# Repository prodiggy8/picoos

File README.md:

##### PicoOS

A bare-metal, very simple operating system for the RP2040/RPI Pico-W written in Rust. Built on [Embassy](https://embassy.dev/).

**Features**

- shell with Unix-like commands
- SD card support with a FAT32-like file system
- text display via DVI, based on [DusterTheFirst's implementation](https://github.com/DusterTheFirst/pico-dvi-rs) 
- PS2 keyboard input via PIO
- run programs with syscalls (print, read)
- load and execute ELF binaries
- CYW43 wireless support
- TCP/IP stack via embassy-net
- debug with websockets

##### Prerequisites

- [Rust](https://rustup.rs/) with `thumbv6m-none-eabi` target
- [probe-rs](https://probe.rs/) for flashing (or [elf2uf2-rs](https://crates.io/crates/elf2uf2-rs) for USB boot mode)
- See PCB above for details on peripherals

##### Build & Run

```bash
cargo run
```

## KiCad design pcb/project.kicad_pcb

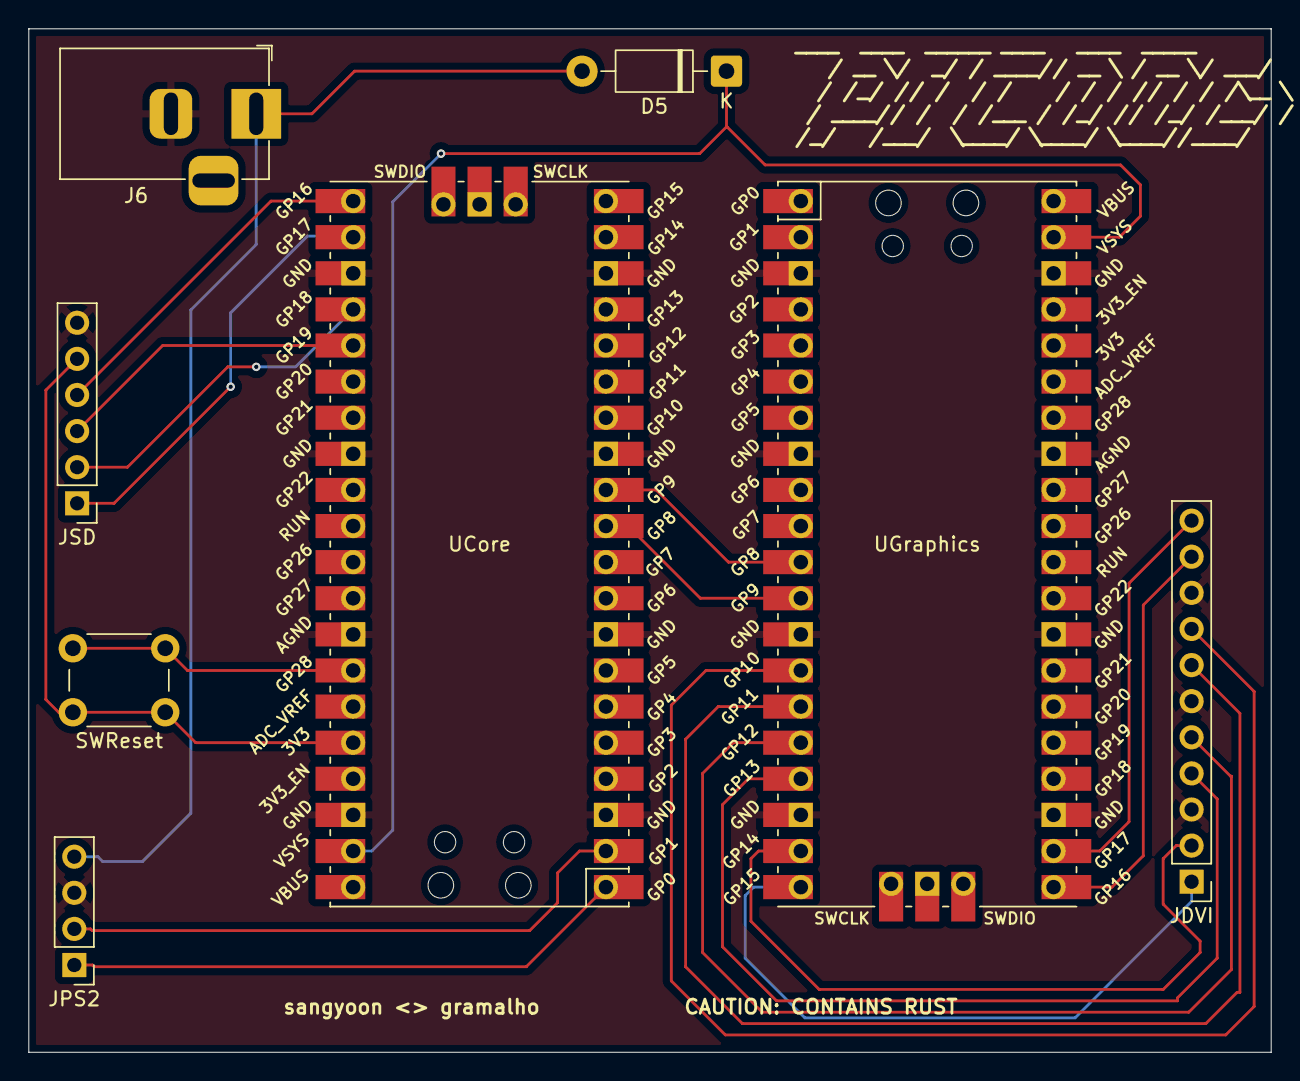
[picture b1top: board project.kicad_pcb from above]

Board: 2 copper layers, 87.4 x 72.0 mm, 8 parts (0 on the bottom side), 21 nets.

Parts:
D5: 1N4001; D_DO-41_SOD81_P10.16mm_Horizontal
J6: Barrel_Jack; BarrelJack_Horizontal
JDVI: Conn_01x11_Pin; PinHeader_1x11_P2.54mm_Vertical
JPS2: Conn_01x04_Pin; PinHeader_1x04_P2.54mm_Vertical
JSD: Conn_01x06_Pin; PinHeader_1x06_P2.54mm_Vertical
SWReset: SW_Push; SW_PUSH_6mm
UCore: Pico W - Core; RPi_Pico_SMD_TH
UGraphics: Pico DVI; RPi_Pico_SMD_TH

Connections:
+3.3V: JSD.5, SWReset.1, UCore.36 (3V3)
+5V: D5.2 (A), J6.1, JPS2.4
CS: JSD.1, UCore.22 (GPIO17)
GND: J6.2, JDVI.3, JDVI.6, JDVI.9, JPS2.3, JSD.6, UCore.3 (GND), UCore.8 (GND), UCore.13 (GND), UCore.18 (GND), UCore.23 (GND), UCore.28 (GND), UCore.33 (AGND), UCore.38 (GND), UGraphics.3 (GND), UGraphics.8 (GND), UGraphics.13 (GND), UGraphics.18 (GND), UGraphics.23 (GND), UGraphics.28 (GND), UGraphics.33 (AGND), UGraphics.38 (GND)
KEY_CLK: JPS2.2, UCore.2 (GPIO1)
KEY_DATA: JPS2.1, UCore.1 (GPIO0)
MISO: JSD.4, UCore.21 (GPIO16)
MOSI: JSD.3, UCore.25 (GPIO19)
POWER: D5.1 (K), UCore.39 (VSYS), UGraphics.39 (VSYS)
RXDVI: UCore.11 (GPIO8), UGraphics.12 (GPIO9)
S0: SWReset.2, UCore.34 (GPIO28_ADC2)
SCK: JSD.2, UCore.24 (GPIO18)
T0+: JDVI.5, UGraphics.16 (GPIO12)
T0-: JDVI.4, UGraphics.17 (GPIO13)
T1+: JDVI.8, UGraphics.14 (GPIO10)
T1-: JDVI.7, UGraphics.15 (GPIO11)
T2+: JDVI.11, UGraphics.22 (GPIO17)
T2-: JDVI.10, UGraphics.21 (GPIO16)
TC+: JDVI.2, UGraphics.19 (GPIO14)
TC-: JDVI.1, UGraphics.20 (GPIO15)
TXDVI: UCore.12 (GPIO9), UGraphics.11 (GPIO8)

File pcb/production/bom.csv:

Designator,Footprint,Quantity,Value,LCSC Part #
D5,D_DO-41_SOD81_P10.16mm_Horizontal,1,1N4001,
J6,BarrelJack_Horizontal,1,Barrel_Jack,
JDVI,PinHeader_1x11_P2.54mm_Vertical,1,Conn_01x11_Pin,
JPS2,PinHeader_1x04_P2.54mm_Vertical,1,Conn_01x04_Pin,
JSD,PinHeader_1x06_P2.54mm_Vertical,1,Conn_01x06_Pin,
SWRESET,SW_PUSH_6mm,1,SW_Push,
UCORE,RPi_Pico_SMD_TH,1,Pico W - Core,
UGRAPHICS,RPi_Pico_SMD_TH,1,Pico DVI,

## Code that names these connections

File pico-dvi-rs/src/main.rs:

#![no_std]
#![no_main]

extern crate alloc;

use core::{arch::global_asm, cell::UnsafeCell, mem::MaybeUninit};

use defmt_rtt as _;
use panic_probe as _; // TODO: remove if you need 5kb of space, since panicking + formatting machinery is huge

use cortex_m::peripheral::NVIC;
use defmt::info;
use dvi::dma::DmaChannelList;
use embedded_alloc::Heap;
use rp_pico::{
    hal::{
        clocks::Clock,
        dma::{Channel, DMAExt, CH0, CH1, CH2, CH3, CH4, CH5},
        gpio::PinState,
        multicore::{Multicore, Stack},
        pwm,
        sio::{Sio, SioFifo},
        watchdog::Watchdog,
        uart::{DataBits, StopBits, UartConfig, UartPeripheral},
    },
    pac::{self, interrupt},
    Pins,
};
use fugit::RateExtU32;

use pac::Interrupt;

use crate::{
    clock::init_clocks,
    dvi::{
        core1_main,
        dma::DmaChannels,
        serializer::{DviClockPins, DviDataPins, DviSerializer},
        timing::VGA_TIMING,
        DviInst,
    },
    render::{init_4bpp_palette, init_display_swapcell, render_line, GLOBAL_PALETTE},
};

mod clock;
mod demo;
mod dvi;
mod link;
mod render;
mod scanlist;

#[global_allocator]
static HEAP: Heap = Heap::empty();

global_asm! {
    include_str!("pre_init.asm"),
    options(raw)
}

struct DviChannels;
impl DmaChannelList for DviChannels {
    type Ch0 = Channel<CH0>;
    type Ch1 = Channel<CH1>;
    type Ch2 = Channel<CH2>;
    type Ch3 = Channel<CH3>;
    type Ch4 = Channel<CH4>;
    type Ch5 = Channel<CH5>;
}

struct DviInstWrapper(UnsafeCell<MaybeUninit<DviInst<DviChannels>>>);

// Safety: access to the instance is indeed shared across threads,
// as it is initialized in the main thread and the interrupt should
// be modeled as another thread (and may be on a different core),
// but only one has access at a time.
//
// Note: this is annoying, `static mut` is more ergonomic (but less
// precise). When `SyncUnsafeCell` is stabilized, use that instead.
unsafe impl Sync for DviInstWrapper {}

static DVI_INST: DviInstWrapper = DviInstWrapper(UnsafeCell::new(MaybeUninit::uninit()));

static mut CORE1_STACK: Stack<256> = Stack::new();

static mut FIFO: MaybeUninit<SioFifo> = MaybeUninit::uninit();

// Separate macro annotated function to make rust-analyzer fixes apply better
#[rp_pico::entry]
fn macro_entry() -> ! {
    entry();
}

const PALETTE: &[u32; 16] = &[
    0x000000, 0xffffff, 0x9d9d9d, 0xe06f8b, 0xbe2633, 0x493c2b, 0xa46422, 0xeb8931, 0xf7e26b,
    0xa3ce27, 0x44891a, 0x2f484e, 0x1b2632, 0x5784, 0x31a2f2, 0xb2dcef,
];

fn entry() -> ! {
    info!("Program start");

    // Test allocations in different memory regions
    rom();
    ram();
    ram_x();
    ram_y();
    defmt::info!("If we have not panicked by now, memory regions probably work well");

    {
        const HEAP_SIZE: usize = 128 * 1024;
        static mut HEAP_MEM: [MaybeUninit<u8>; HEAP_SIZE] = [MaybeUninit::uninit(); HEAP_SIZE];
        unsafe { HEAP.init(HEAP_MEM.as_ptr() as usize, HEAP_SIZE) }
    }

    let mut peripherals = pac::Peripherals::take().unwrap();
    //let core_peripherals = pac::CorePeripherals::take().unwrap();

    sysinfo(&peripherals.SYSINFO);

    let mut watchdog = Watchdog::new(peripherals.WATCHDOG);
    let single_cycle_io = Sio::new(peripherals.SIO);

    let timing = VGA_TIMING;

    // External high-speed crystal on the pico board is 12Mhz
    let _clocks = init_clocks(
        peripherals.XOSC,
        peripherals.ROSC,
        peripherals.CLOCKS,
        peripherals.PLL_SYS,
        peripherals.PLL_USB,
        &mut peripherals.RESETS,
        &mut watchdog,
        timing.bit_clk,
    );

    let pins = Pins::new(
        peripherals.IO_BANK0,
        peripherals.PADS_BANK0,
        single_cycle_io.gpio_bank0,
        &mut peripherals.RESETS,
    );

    let led_pin = pins.led.into_push_pull_output_in_state(PinState::Low);

    let pwm_slices = pwm::Slices::new(peripherals.PWM, &mut peripherals.RESETS);
    let dma = peripherals.DMA.split(&mut peripherals.RESETS);

    let (data_pins, clock_pins) = {
        (
            DviDataPins {
                // 0
                blue_pos: pins.gpio12.into_function(),
                blue_neg: pins.gpio13.into_function(),
                // 1
                green_pos: pins.gpio10.into_function(),
                green_neg: pins.gpio11.into_function(),
                // 2
                red_pos: pins.gpio17.into_function(),
                red_neg: pins.gpio16.into_function(),
            },
            DviClockPins {
                clock_pos: pins.gpio14.into_function(),
                clock_neg: pins.gpio15.into_function(),
                pwm_slice: pwm_slices.pwm7,
            },
        )
    };

    let serializer = DviSerializer::new(
        peripherals.PIO0,
        &mut peripherals.RESETS,
        data_pins,
        clock_pins,
    );

    let dma_channels = DmaChannels::new(
        (dma.ch0, dma.ch1, dma.ch2, dma.ch3, dma.ch4, dma.ch5),
        serializer.tx(),
    );

    {
        // Safety: the DMA_IRQ_0 handler is not enabled yet. We have exclusive access to this static.
        let inst = unsafe { (*DVI_INST.0.get()).write(DviInst::new(timing, dma_channels)) };
        inst.setup_dma();
        inst.start();
    }
    let mut fifo = single_cycle_io.fifo;
    let mut mc = Multicore::new(&mut peripherals.PSM, &mut peripherals.PPB, &mut fifo);
    let cores = mc.cores();
    let core1 = &mut cores[1];
    core1
        .spawn(unsafe { &mut CORE1_STACK.mem }, move || {
            core1_main(serializer)
        })
        .unwrap();
    // Safety: enable interrupt for fifo to receive line render requests.
    // Transfer ownership of this end of the fifo to the interrupt handler.
    unsafe {
        FIFO = MaybeUninit::new(fifo);
        NVIC::unmask(Interrupt::SIO_IRQ_PROC0);
    }
    init_display_swapcell(640);

    unsafe {
        init_4bpp_palette(&mut GLOBAL_PALETTE, PALETTE);
    }

    let uart_pins = (
        pins.gpio8.into_function::<rp_pico::hal::gpio::FunctionUart>(),
        pins.gpio9.into_function::<rp_pico::hal::gpio::FunctionUart>(),
    );

    let mut uart = UartPeripheral::new(peripherals.UART1, uart_pins, &mut peripherals.RESETS)
        .enable(
            UartConfig::new(9600.Hz(), DataBits::Eight, None, StopBits::One),
            _clocks.peripheral_clock.freq(),
        )
        .unwrap();

    demo::demo(led_pin, &mut uart);
}

fn sysinfo(sysinfo: &pac::SYSINFO) {
    let is_fpga = sysinfo.platform.read().fpga().bit();
    let is_asic = sysinfo.platform.read().asic().bit();
    let git_hash = sysinfo.gitref_rp2040.read().bits();
    let manufacturer = sysinfo.chip_id.read().manufacturer().bits();
    let part = sysinfo.chip_id.read().part().bits();
    let revision = sysinfo.chip_id.read().revision().bits();

    info!(
        "SYSINFO
platform:
    FPGA: {=bool}
    ASIC: {=bool}
gitref_rp2040: {=u32:x}
chip_id:
    manufacturer: {=u16:X}
    part:         {=u16}
    revision:     {=u8}",
        is_fpga, is_asic, git_hash, manufacturer, part, revision
    );
}

// Functions and statics are placed in rom by default
fn rom() {
    let ptr = rom as fn() as *const ();
    defmt::assert!(
        (0x10000100..0x20000000).contains(&(ptr as u32)),
        "rom fn is placed at {} which is not in FLASH",
        ptr
    );
}

// This function will be placed in ram
#[link_section = link!(ram, ram)]
fn ram() {
    let ptr = ram as fn() as *const ();
    defmt::assert!(
        (0x20000000..0x20040000).contains(&(ptr as u32)),
        "ram fn is placed at {} which is not in RAM",
        ptr
    );
}

// This function will be placed in ram
#[link_section = link!(scratch x, ram_x)]
fn ram_x() {
    let ptr = ram_x as fn() as *const ();
    defmt::assert!(
        (0x20040000..0x20041000).contains(&(ptr as u32)),
        "ram_x fn is placed at {} which is not in SCRATCH_X",
        ptr
    );
}

// This function will be placed in ram
#[link_section = link!(scratch y, ram_y)]
fn ram_y() {
    let ptr = ram_y as fn() as *const ();
    defmt::assert!(
        (0x20041000..0x20042000).contains(&(ptr as u32)),
        "ram_y fn is placed at {} which is not in SCRATCH_Y",
        ptr
    );
}

/// Called by the system only when core 1 is overloaded and can't handle all the rendering work, and requests core 0 to render one scan line worth of content.
#[link_section = ".data"]
#[interrupt]
fn SIO_IRQ_PROC0() {
    // Safety: this interrupt handler has exclusive access to this
    // end of the fifo.
    let fifo = unsafe { FIFO.assume_init_mut() };
    while let Some(line_ix) = fifo.read() {
        // Safety: exclusive access to the line buffer is granted
        // when the render is scheduled to a core.
        unsafe { render_line(line_ix) };
    }
}

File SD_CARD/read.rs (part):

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
    // SPI0 pins for SD card
    //
    // SD SCK  -> GPIO18
    // SD MOSI -> GPIO19
    // SD MISO -> GPIO16
    // SD CS   -> GPIO17
    let spi_sck = pins.gpio18.into_function::<FunctionSpi>();
    let spi_mosi = pins.gpio19.into_function::<FunctionSpi>();
    let spi_miso = pins.gpio16.into_function::<FunctionSpi>();
    let spi_pins = (spi_mosi, spi_miso, spi_sck);

    let mut spi = Spi::<_, _, _, 8>::new(pac.SPI0, spi_pins).init(
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        MODE_0,
    );

    let mut sd_cs = pins.gpio17.into_push_pull_output();
    let _ = sd_cs.set_high(); // deselect

    info!("Init SD...");
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
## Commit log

2025-11-25 First commit: socket with screen
2025-11-25 Server files
2025-11-25 Initialize cargo.toml for os-keyboard project
    Added package metadata and dependencies for the os-keyboard project.
2025-11-25 Add SD card support over SPI for RP Pico
    This file implements SD card support over SPI for the RP Pico, including initialization, command sending, and reading blocks.
2025-11-25 Improve SD card initialization and write logic
    Enhanced SD card initialization and write operations with improved retry logic and error handling.
2025-11-26 Add SD card read functionality
    Implement SD card reading functionality with SPI interface, including initialization and reading a block of data.
2025-11-26 Integration between socket & PS2
2025-11-26 Final checkpoint version
2025-11-30 Create FILE_SYSTEM
2025-11-30 Add sd_test folder with SD card filesystem implementation
2025-11-30 Update sd_test
2025-12-06 Add build script to manage linker script
2025-12-08 Rebase: modularized code & integrated previous kernel with DVI output
2025-12-10 working demo: exec
2025-12-10 Demo: read & write eval working
2025-12-10 updated code
2025-12-11 Final demo
2026-03-21 Add PCB KiCad project; vendor pico-dvi-rs as regular files
    Replace broken pico-dvi-rs gitlink (no .gitmodules) with full tree so
    checkout/pull no longer errors. Note: avoid 'git commit -- pico-dvi-rs' on
    the old history—that pathspec triggers submodule logic and fails.
    Made-with: Cursor
2026-03-21 readme
2026-03-22 removing test files
2026-05-03 Add BSD 3-Clause License file
